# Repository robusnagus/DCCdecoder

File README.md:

## Dekoder funkcji DCC ##

Dekoder funkcji DCC z przeznaczeniem do sterowania oświetleniem wagonów.
Część sprzętowa w przygotowaniu.

### Elementy projektu ###

**funcdec_proto3208.X**  
Prototypowe oprogramowanie dla ATMega3208 (0-series). Odebrane pakiety DCC są dodatkowo dekodowane do HEX i wysyłane na port szeregowy.  
**funcdec_mk1.X**  
Oprogramowanie dla ATTiny 1614 (1-series).  

Tryby pracy: tylko DCC.  
Tryby programowania: tryb serwisowy na torze programującym.  
Adresowanie: długie (domyślnie) i krótkie.  
Wyjścia funkcyjne: zależnie od implementacji sprzętowej.

### Wersje sprzętowe ###

**Dekoder uniwersalny.**  
6 wyjść funkcyjnych z indywidualnym ściemnianiem.

### Kompilacja oprogramowania ###

Projekt MPLABX (wersja 5.35) z kompilatorem gcc dołączonym do pakietu XC8 (wersja 2.10). Użyto pakietów definicji dostarczonych wraz z MPLABX.

### Obsługa dekodera ###

| CV   | Przeznaczenie                                    | Zakres | Wart. |
|------|--------------------------------------------------|--------|-------|
| 1    | Adres pojazdu, krótki                            |        |       |
| 7    | Wersja dekodera, tylko do odczytu                | n/d    | n/d   |
| 8    | Kod producenta, tylko do odczytu                 | n/d    | n/d   |
| 17   | Adres pojazdu, długi                             |        |       |
| 18   |                                                  |        |       |
| 29   | Konfiguracja dekodera                            |        |       |
| 33   | Mapowanie funkcji dla wyjścia A.                 |        |       |
| 34   | Mapowanie funkcji dla wyjścia A.                 |        |       |
| 45   | Deaktywacja wyjść dla kierunku ruchu: do przodu. |        |       |
| 47   | Deaktywacja wyjść dla kierunku ruchu: do tyłu.   |        |       |
| 49   | Jasność dla wyjścia A.                           | 0-63   | 63    |

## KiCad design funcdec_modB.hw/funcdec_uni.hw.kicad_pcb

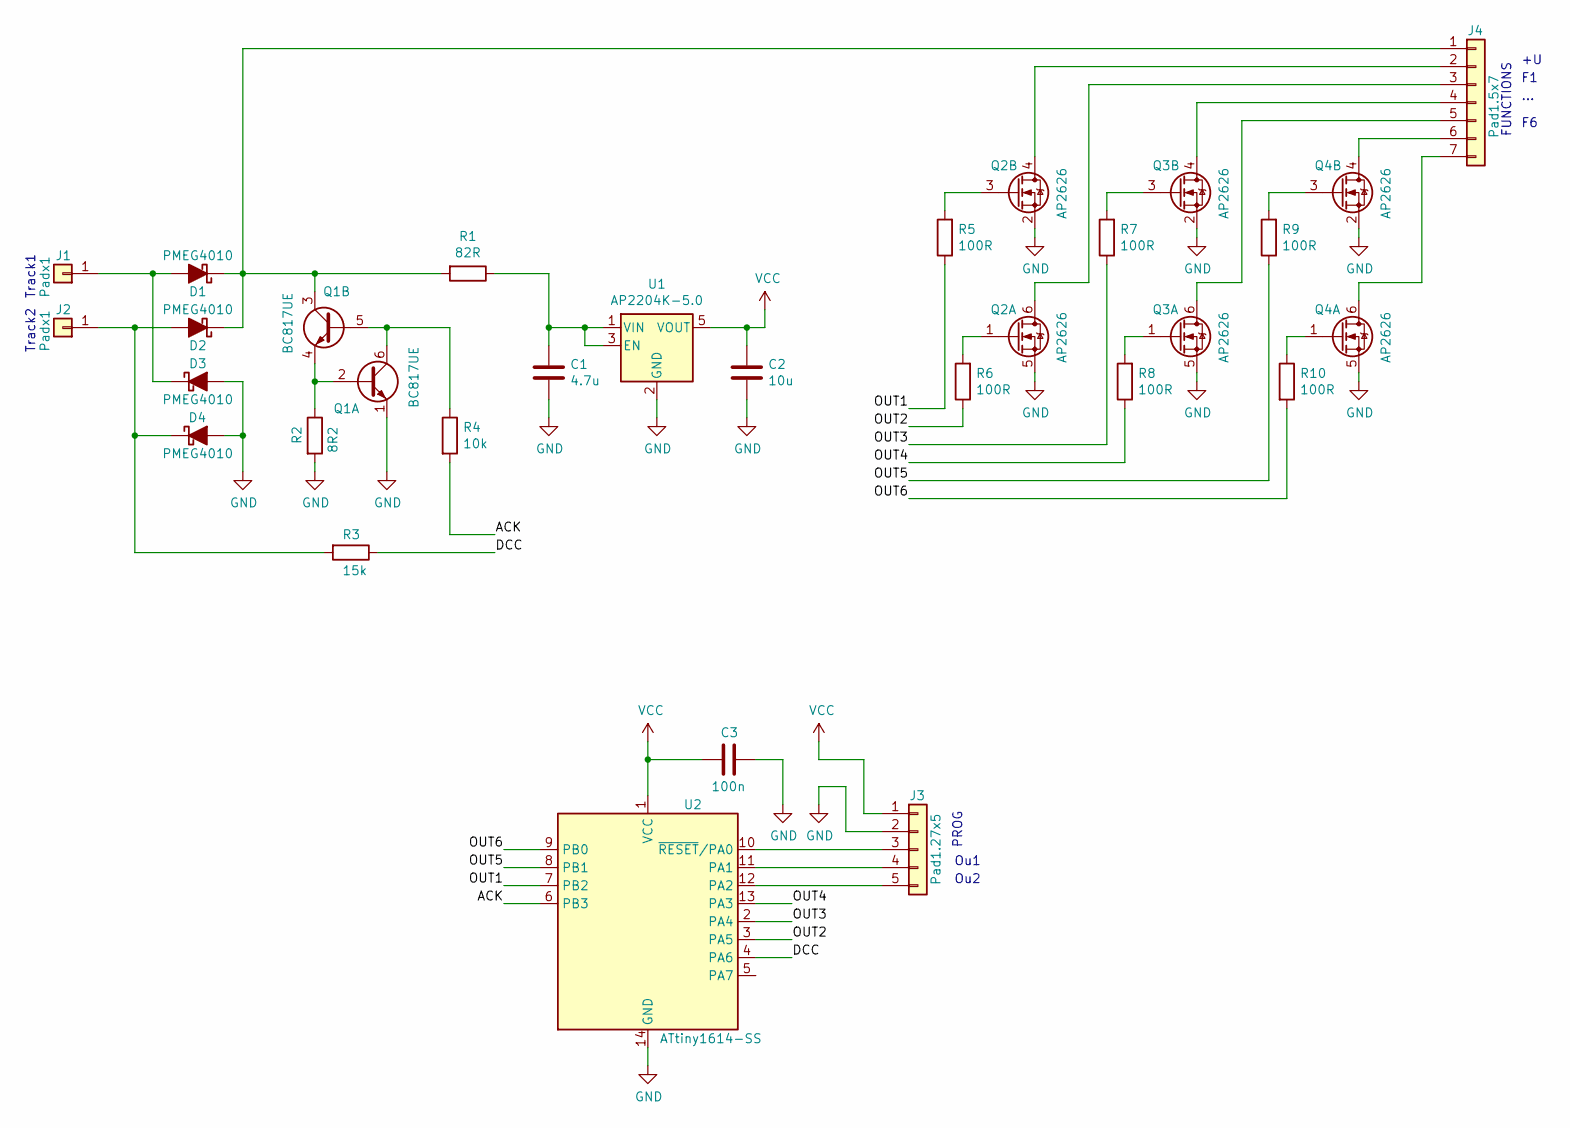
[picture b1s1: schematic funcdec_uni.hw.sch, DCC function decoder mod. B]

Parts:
C1: 4.7u; SMD_1206_HS
C2: 10u; SMD_1206_HS
C3: 100n; SMD_0805_HS
D1, D2, D3, D4: PMEG4010; SOD323_HS
J1, J2: Padx1; Array_1-27mm_1X1_SMD
J3: Pad1.27x5; Array_1-27mm_1X5_SMD
J4: Pad1.5x7; Array_1-50mm_1X7_SMD
Q1: BC817UE; SOT23-6_HS
Q2, Q3, Q4: AP2626; SOT23-6_HS
R1: 82R; SMD_1206_HS
R2: 8R2; SMD_0805_HS
R3: 15k; SMD_0805_HS
R4: 10k; SMD_0805_HS
R5, R6, R7, R8, R9, R10: 100R; SMD_0805_HS
U1: AP2204K-5.0; SOT23-5_HS
U2: ATtiny1614-SS; SOIC14_HS

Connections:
/ACK: R4.2, U2.6 (PB3)
/DCC: R3.1, U2.4 (PA6)
/OUT1: R5.1, U2.7 (PB2)
/OUT2: R6.1, U2.3 (PA5)
/OUT3: R7.1, U2.2 (PA4)
/OUT4: R8.1, U2.13 (PA3)
/OUT5: R9.1, U2.8 (PB1)
/OUT6: R10.2, U2.9 (PB0)
GND: C1.1, C2.2, C3.1, D3.2 (A), D4.2 (A), J3.2, Q1.1 (E1), Q2.2 (S), Q2.5 (S), Q3.2 (S), Q3.5 (S), Q4.2 (S), Q4.5 (S), R2.2, U1.2 (GND), U2.14 (GND)
unnamed: C1.2, R1.1, U1.1 (VIN), U1.3 (EN)
unnamed: D1.1 (K), D2.1 (K), J4.1, Q1.3 (C2), R1.2
unnamed: D1.2 (A), D3.1 (K), J1.1
unnamed: D2.2 (A), D4.1 (K), J2.1, R3.2
unnamed: J3.3, U2.10 (~RESET~/PA0)
unnamed: J3.4, U2.11 (PA1)
unnamed: J3.5, U2.12 (PA2)
unnamed: J4.2, Q2.4 (D)
unnamed: J4.3, Q2.6 (D)
unnamed: J4.4, Q3.4 (D)
unnamed: J4.5, Q3.6 (D)
unnamed: J4.6, Q4.4 (D)
unnamed: J4.7, Q4.6 (D)
unnamed: Q1.2 (B1), Q1.4 (E2), R2.1
unnamed: Q1.5 (B2), Q1.6 (C1), R4.1
unnamed: Q2.1 (G), R6.2
unnamed: Q2.3 (G), R5.2
unnamed: Q3.1 (G), R8.2
unnamed: Q3.3 (G), R7.2
unnamed: Q4.1 (G), R10.1
unnamed: Q4.3 (G), R9.2
VCC: C2.1, C3.2, J3.1, U1.5 (VOUT), U2.1 (VCC)

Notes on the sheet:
PROG
Track1
Track2
FUNCTIONS
...
Ou1
Ou2

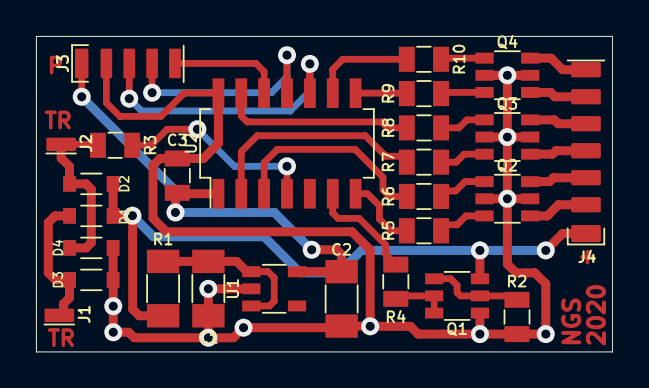
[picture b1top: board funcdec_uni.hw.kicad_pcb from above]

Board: 2 copper layers, 32.0 x 17.5 mm, 27 parts (0 on the bottom side), 31 nets.

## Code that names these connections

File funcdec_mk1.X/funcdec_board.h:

//
// DCC function decoder
//
// Copyright 2020 Robert Nagowski
//
// This program is free software: you can redistribute it and/or modify
// it under the terms of the GNU General Public License as published by
// the Free Software Foundation, either version 3 of the License, or
// (at your option) any later version.
// See gpl-3.0.md file for details.
//

#ifndef FUNCDEC_BOARD_H
#define	FUNCDEC_BOARD_H

#include <avr/io.h>
#include <avr/interrupt.h>

#include "funcdec_config.h"

// HW config for ATTiny
// DCCIN            PA1
// OUT_ACK          PA6
// universal decoder
// 6 outputs with independent dimming
// AUXD_A AUXD_B    PB2 PA5
// AUXD_C AUXD_D    PA4 PA3
// AUXD_E AUXD_F    PB1 PB0

#define BOARD_AUXDA                 0
#define BOARD_AUXDA_On()            PORTB.OUTSET = (1 << PIN2_bp)
#define BOARD_AUXDA_Off()           PORTB.OUTCLR = (1 << PIN2_bp)
#define BOARD_AUXDA_Toggle()        PORTB.OUTTGL = (1 << PIN2_bp)
#define BOARD_AUXDB                 1
#define BOARD_AUXDB_On()            PORTA.OUTSET = (1 << PIN5_bp)
#define BOARD_AUXDB_Off()           PORTA.OUTCLR = (1 << PIN5_bp)
#define BOARD_AUXDB_Toggle()        PORTA.OUTTGL = (1 << PIN5_bp)
#define BOARD_AUXDC                 2
#define BOARD_AUXDC_On()            PORTA.OUTSET = (1 << PIN4_bp)
#define BOARD_AUXDC_Off()           PORTA.OUTCLR = (1 << PIN4_bp)
#define BOARD_AUXDC_Toggle()        PORTA.OUTTGL = (1 << PIN4_bp)
#define BOARD_AUXDD                 3
#define BOARD_AUXDD_On()            PORTA.OUTSET = (1 << PIN3_bp)
#define BOARD_AUXDD_Off()           PORTA.OUTCLR = (1 << PIN3_bp)
#define BOARD_AUXDD_Toggle()        PORTA.OUTTGL = (1 << PIN3_bp)
#define BOARD_AUXDE                 4
#define BOARD_AUXDE_On()            PORTB.OUTSET = (1 << PIN1_bp)
#define BOARD_AUXDE_Off()           PORTB.OUTCLR = (1 << PIN1_bp)
#define BOARD_AUXDE_Toggle()        PORTB.OUTTGL = (1 << PIN1_bp)
#define BOARD_AUXDF                 5
#define BOARD_AUXDF_On()            PORTB.OUTSET = (1 << PIN0_bp)
#define BOARD_AUXDF_Off()           PORTB.OUTCLR = (1 << PIN0_bp)
#define BOARD_AUXDF_Toggle()        PORTB.OUTTGL = (1 << PIN0_bp)

#define BOARD_OUTACK_On()           PORTA.OUTSET = (1 << PIN6_bp)
#define BOARD_OUTACK_Off()          PORTA.OUTCLR = (1 << PIN6_bp)
#define BOARD_OUTACK_Toggle()       PORTA.OUTTGL = (1 << PIN6_bp)

#define BOARD_DCCREC_Handler()      ISR(TCB0_INT_vect)
#define BOARD_DCCREC_SetReady()     TCB0.INTFLAGS = (1 << TCB_CAPT_bp)
#define BOARD_DCCREC_GetBitTime()   TCB0.CCMP

#define BOARD_PWM_Enable(x)         TCA0.SPLIT.CTRLB = x
#define BOARD_PWM_NONE              0x00
#define BOARD_PWMA_ENABLE           (1 << TCA_SPLIT_LCMP2EN_bp)
#define BOARD_PWMB_ENABLE           (1 << TCA_SPLIT_HCMP2EN_bp)
#define BOARD_PWMC_ENABLE           (1 << TCA_SPLIT_HCMP1EN_bp)
#define BOARD_PWMD_ENABLE           (1 << TCA_SPLIT_HCMP0EN_bp)
#define BOARD_PWME_ENABLE           (1 << TCA_SPLIT_LCMP1EN_bp)
#define BOARD_PWMF_ENABLE           (1 << TCA_SPLIT_LCMP0EN_bp)
#define BOARD_PWMA_SetDutyCycle(x)  TCA0.SPLIT.LCMP2 = x
#define BOARD_PWMB_SetDutyCycle(x)  TCA0.SPLIT.HCMP2 = x
#define BOARD_PWMC_SetDutyCycle(x)  TCA0.SPLIT.HCMP1 = x
#define BOARD_PWMD_SetDutyCycle(x)  TCA0.SPLIT.HCMP0 = x
#define BOARD_PWME_SetDutyCycle(x)  TCA0.SPLIT.LCMP1 = x
#define BOARD_PWMF_SetDutyCycle(x)  TCA0.SPLIT.LCMP0 = x

#define _PROTECTED_WRITE(reg, value)				\
    __asm__ __volatile__("out %[ccp], %[ccp_ioreg]" "\n\t"	\
                         "sts %[ioreg], %[val]"			    \
                         :					                \
                         : [ccp] "I" (_SFR_IO_ADDR(CCP)),	\
                         [ccp_ioreg] "d" ((uint8_t)CCP_IOREG_gc),	\
                         [ioreg] "n" (_SFR_MEM_ADDR(reg)),	\
                         [val] "r" ((uint8_t)value))

#define SYS_EnableInterrupts()     __asm__ __volatile__ ( "sei" ::: "memory")

#endif	// FUNCDEC_BOARD_H

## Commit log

2020-03-05 master
    initial commit
2020-04-06 MPLAB update
2020-05-15 initial description
2020-05-15 remove heartbit
2020-05-15 update 4 target hw
2020-05-15 unified with target hw
2020-05-15 update for target hw
2020-05-18 editorial corrections
2020-05-18 compiler update
2020-05-18 ack circuit correction
2020-05-18 small update
2020-10-28 corrections and file rename for manf
